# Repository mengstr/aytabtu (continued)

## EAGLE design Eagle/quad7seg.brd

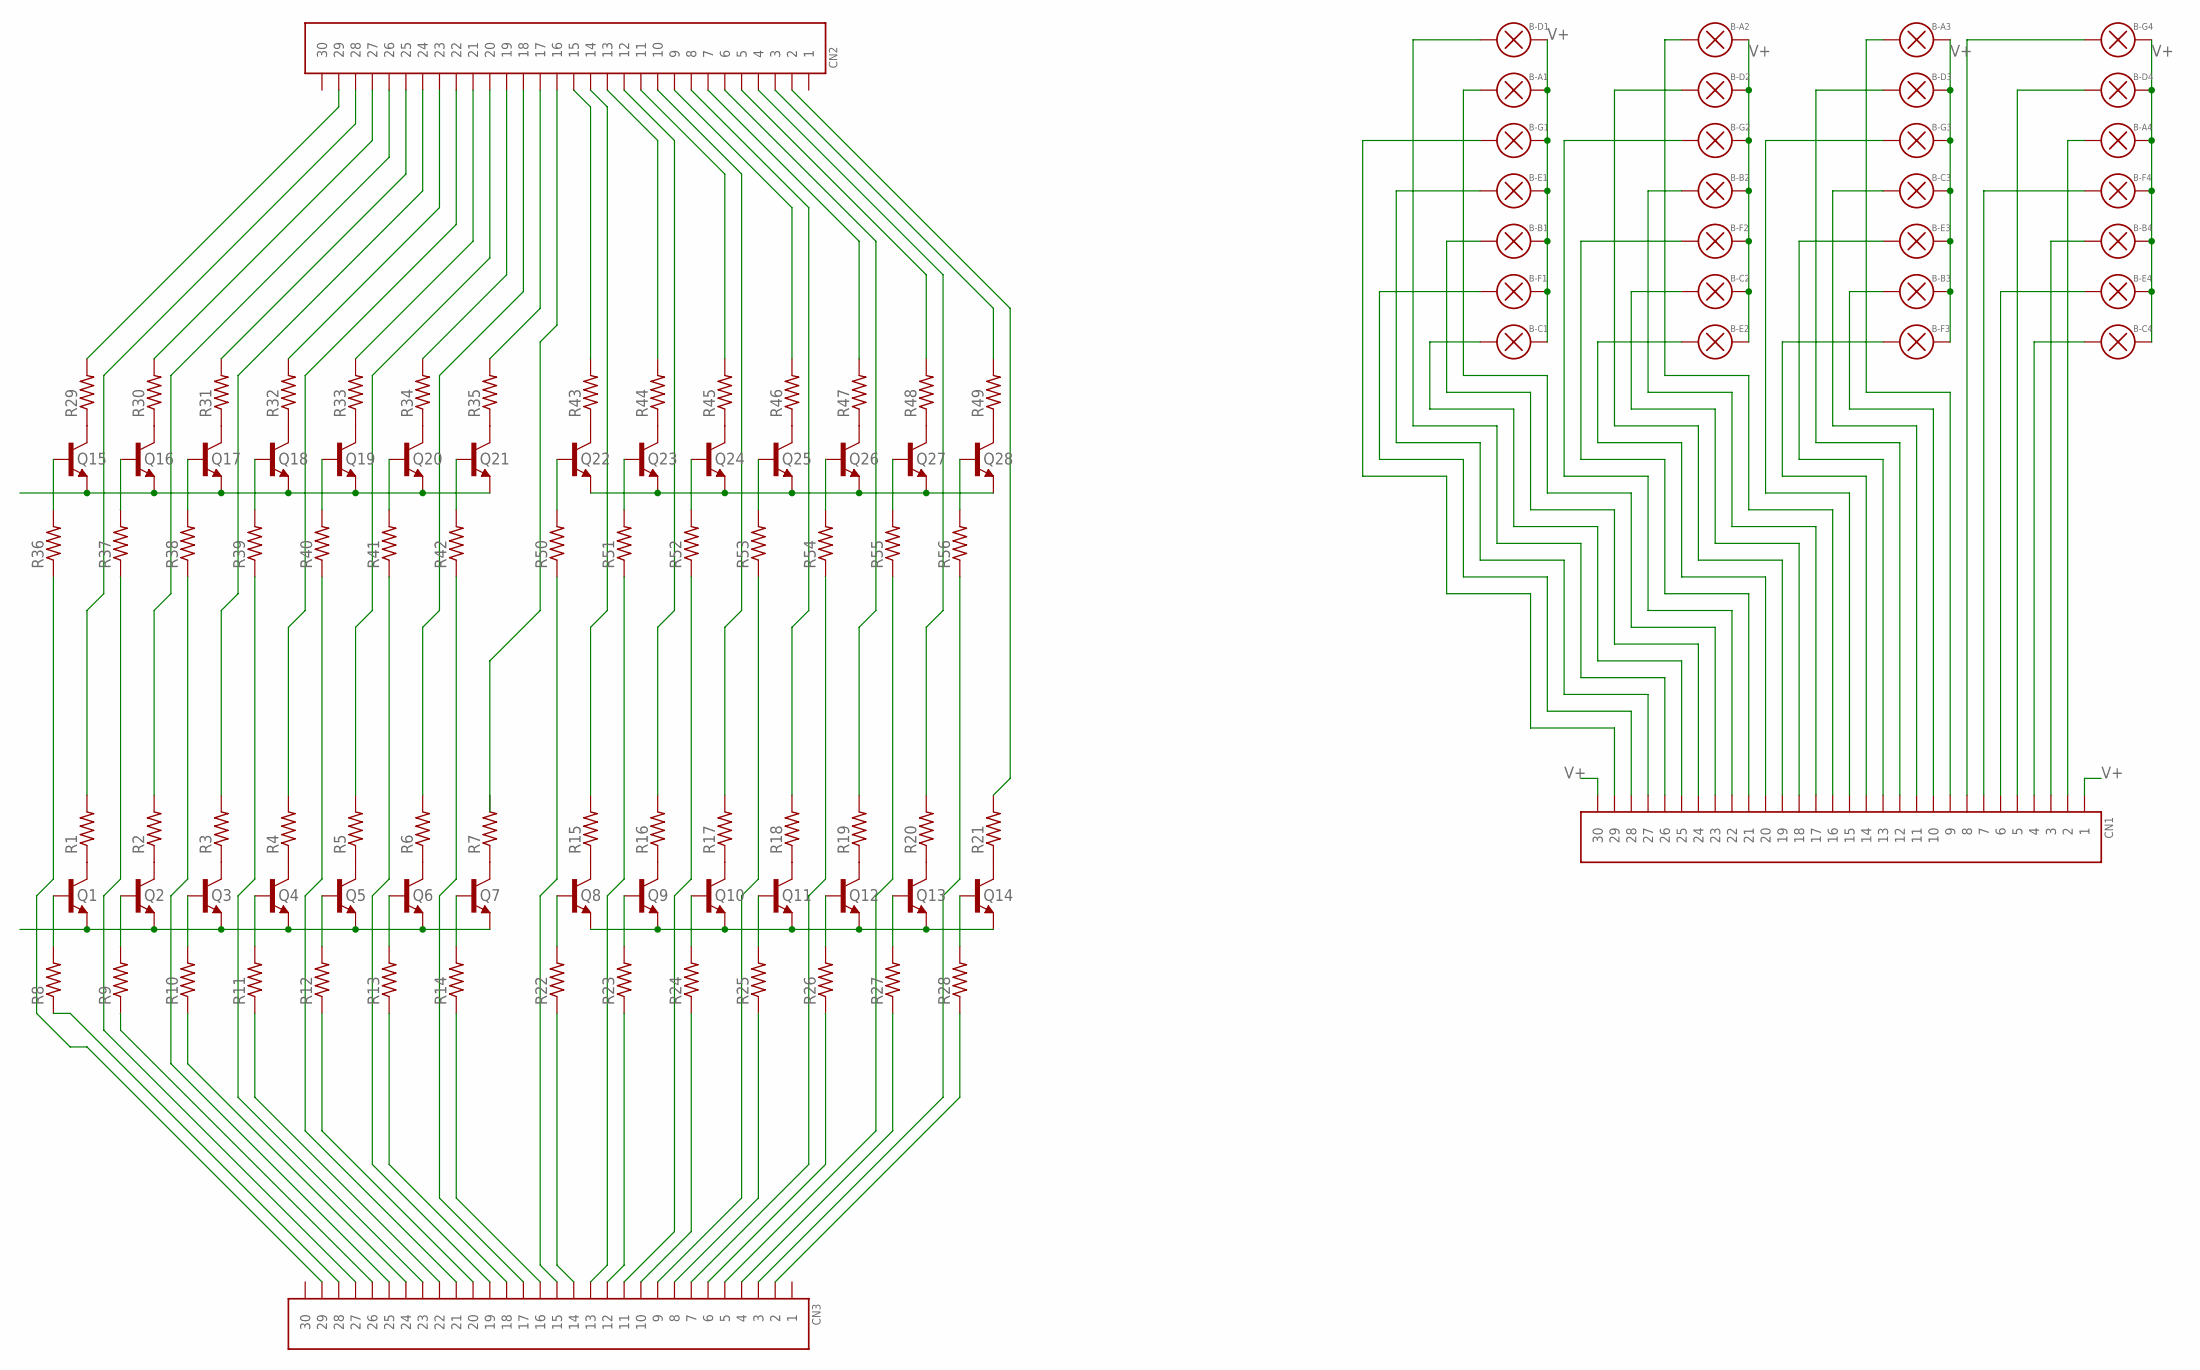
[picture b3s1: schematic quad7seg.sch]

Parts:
B-A1, B-A2, B-A3, B-A4: BULB-N; 4X11BULB1
B-B1, B-B2, B-B3, B-B4: BULB-F; 4X11BULB2
B-C1, B-C2, B-C3, B-C4: BULB-F; 4X11BULB2
B-D1, B-D2, B-D3, B-D4: BULB-N; 4X11BULB1
B-E1, B-E2, B-E3, B-E4: BULB-F; 4X11BULB2
B-F1, B-F2, B-F3, B-F4: BULB-F; 4X11BULB2
B-G1, B-G2, B-G3, B-G4: BULB-N; 4X11BULB1
CN1, CN2, CN3: HD30
Q1, Q2, Q3, Q4, Q5, Q6, Q7, Q8, Q9, Q10, Q11, Q12, Q13, Q14, Q15, Q16, Q17, Q18, Q19, Q20, Q21, Q22, Q23, Q24, Q25, Q26, Q27, Q28: 2N3904-1; TO92BH
R1, R2, R3, R4, R5, R6, R7, R8, R9, R10, R11, R12, R13, R14, R15, R16, R17, R18, R19, R20, R21, R22, R23, R24, R25, R26, R27, R28, R29, R30, R31, R32, R33, R34, R35, R36, R37, R38, R39, R40, R41, R42, R43, R44, R45, R46, R47, R48, R49, R50, R51, R52, R53, R54, R55, R56: R1/8-7.6MM; R0125-7.6

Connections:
GND: Q1.1 (E), Q2.1 (E), Q3.1 (E), Q4.1 (E), Q5.1 (E), Q6.1 (E), Q7.1 (E), Q8.1 (E), Q9.1 (E), Q10.1 (E), Q11.1 (E), Q12.1 (E), Q13.1 (E), Q14.1 (E), Q15.1 (E), Q16.1 (E), Q17.1 (E), Q18.1 (E), Q19.1 (E), Q20.1 (E), Q21.1 (E), Q22.1 (E), Q23.1 (E), Q24.1 (E), Q25.1 (E), Q26.1 (E), Q27.1 (E), Q28.1 (E)
unnamed: Q1.3 (C), R1.1
unnamed: Q2.3 (C), R2.1
unnamed: Q3.3 (C), R3.1
unnamed: Q4.3 (C), R4.1
unnamed: Q5.3 (C), R5.1
unnamed: Q6.3 (C), R6.1
unnamed: Q7.3 (C), R7.1
unnamed: Q1.2 (B), R8.2
unnamed: Q2.2 (B), R9.2
unnamed: Q3.2 (B), R10.2
unnamed: Q4.2 (B), R11.2
unnamed: Q5.2 (B), R12.2
unnamed: Q6.2 (B), R13.2
unnamed: Q7.2 (B), R14.2
unnamed: B-A4.P$1, CN1.P$2 (2)
unnamed: Q8.3 (C), R15.1
unnamed: Q9.3 (C), R16.1
unnamed: Q10.3 (C), R17.1
unnamed: Q11.3 (C), R18.1
unnamed: Q12.3 (C), R19.1
unnamed: Q13.3 (C), R20.1
unnamed: Q14.3 (C), R21.1
unnamed: Q8.2 (B), R22.2
unnamed: Q9.2 (B), R23.2
unnamed: Q10.2 (B), R24.2
unnamed: Q11.2 (B), R25.2
unnamed: Q12.2 (B), R26.2
unnamed: Q13.2 (B), R27.2
unnamed: Q14.2 (B), R28.2
unnamed: B-B4.P$1, CN1.P$3 (3)
unnamed: Q15.3 (C), R29.1
unnamed: Q16.3 (C), R30.1
unnamed: Q17.3 (C), R31.1
unnamed: Q18.3 (C), R32.1
unnamed: Q19.3 (C), R33.1
unnamed: Q20.3 (C), R34.1
unnamed: Q21.3 (C), R35.1
unnamed: Q15.2 (B), R36.2
unnamed: Q16.2 (B), R37.2
unnamed: Q17.2 (B), R38.2
unnamed: Q18.2 (B), R39.2
unnamed: Q19.2 (B), R40.2
unnamed: Q20.2 (B), R41.2
unnamed: Q21.2 (B), R42.2
unnamed: B-C4.P$1, CN1.P$4 (4)
unnamed: Q22.3 (C), R43.1
unnamed: Q23.3 (C), R44.1
unnamed: Q24.3 (C), R45.1
unnamed: Q25.3 (C), R46.1
unnamed: Q26.3 (C), R47.1
unnamed: Q27.3 (C), R48.1
unnamed: Q28.3 (C), R49.1
unnamed: Q22.2 (B), R50.2
unnamed: Q23.2 (B), R51.2
unnamed: Q24.2 (B), R52.2
unnamed: Q25.2 (B), R53.2
unnamed: Q26.2 (B), R54.2
unnamed: Q27.2 (B), R55.2
unnamed: Q28.2 (B), R56.2
unnamed: CN3.P$29 (29), R36.1
unnamed: CN2.P$3 (3), R49.2
unnamed: CN2.P$5 (5), R48.2
unnamed: CN2.P$7 (7), R47.2
unnamed: CN2.P$9 (9), R46.2
unnamed: CN2.P$11 (11), R45.2
unnamed: CN2.P$13 (13), R44.2
unnamed: CN2.P$15 (15), R43.2
unnamed: CN2.P$17 (17), R35.2
unnamed: CN2.P$19 (19), R34.2
unnamed: CN2.P$21 (21), R33.2
unnamed: CN2.P$23 (23), R32.2
unnamed: CN2.P$25 (25), R31.2
unnamed: CN2.P$27 (27), R30.2
unnamed: CN2.P$29 (29), R29.2
unnamed: CN2.P$2 (2), R21.2
unnamed: CN2.P$4 (4), R20.2
unnamed: CN2.P$6 (6), R19.2
unnamed: CN2.P$8 (8), R18.2
unnamed: CN2.P$10 (10), R17.2
unnamed: CN2.P$12 (12), R16.2
unnamed: CN2.P$14 (14), R15.2
unnamed: CN2.P$18 (18), R6.2
unnamed: CN2.P$20 (20), R5.2
unnamed: CN2.P$22 (22), R4.2
unnamed: CN2.P$24 (24), R3.2
unnamed: CN2.P$26 (26), R2.2
unnamed: CN2.P$28 (28), R1.2
unnamed: CN3.P$2 (2), R28.1
unnamed: CN3.P$4 (4), R27.1
unnamed: CN3.P$6 (6), R26.1
unnamed: CN3.P$8 (8), R25.1
unnamed: CN3.P$10 (10), R24.1
unnamed: CN3.P$12 (12), R23.1
unnamed: CN3.P$14 (14), R22.1
unnamed: CN3.P$16 (16), R14.1
unnamed: CN3.P$18 (18), R13.1
unnamed: CN3.P$20 (20), R12.1
unnamed: CN3.P$22 (22), R11.1
unnamed: CN3.P$24 (24), R10.1
unnamed: CN3.P$26 (26), R9.1
unnamed: CN3.P$28 (28), R8.1
unnamed: CN3.P$3 (3), R56.1
unnamed: CN3.P$5 (5), R55.1
unnamed: CN3.P$7 (7), R54.1
unnamed: CN3.P$9 (9), R53.1
unnamed: CN3.P$11 (11), R52.1
unnamed: CN3.P$13 (13), R51.1
unnamed: CN3.P$15 (15), R50.1
unnamed: CN3.P$17 (17), R42.1
unnamed: CN3.P$19 (19), R41.1
unnamed: CN3.P$21 (21), R40.1
unnamed: CN3.P$23 (23), R39.1
unnamed: CN3.P$25 (25), R38.1
unnamed: CN3.P$27 (27), R37.1
unnamed: B-D4.P$1, CN1.P$5 (5)
unnamed: B-E4.P$1, CN1.P$6 (6)
unnamed: B-F4.P$1, CN1.P$7 (7)
unnamed: B-G4.P$1, CN1.P$8 (8)
unnamed: B-A3.P$1, CN1.P$9 (9)
unnamed: B-B3.P$1, CN1.P$10 (10)
unnamed: B-C3.P$1, CN1.P$11 (11)
unnamed: B-D3.P$1, CN1.P$12 (12)
unnamed: B-E3.P$1, CN1.P$13 (13)
unnamed: B-F3.P$1, CN1.P$14 (14)
unnamed: B-G3.P$1, CN1.P$15 (15)
unnamed: B-A2.P$1, CN1.P$16 (16)
unnamed: B-B2.P$1, CN1.P$17 (17)
unnamed: B-C2.P$1, CN1.P$18 (18)
unnamed: B-D2.P$1, CN1.P$19 (19)
unnamed: B-E2.P$1, CN1.P$20 (20)
unnamed: B-F2.P$1, CN1.P$21 (21)
unnamed: B-G2.P$1, CN1.P$22 (22)
unnamed: B-A1.P$1, CN1.P$23 (23)
unnamed: B-B1.P$1, CN1.P$24 (24)
unnamed: B-C1.P$1, CN1.P$25 (25)
unnamed: B-D1.P$1, CN1.P$26 (26)
unnamed: B-E1.P$1, CN1.P$27 (27)
unnamed: B-F1.P$1, CN1.P$28 (28)
unnamed: B-G1.P$1, CN1.P$29 (29)
V+: B-A1.P$2, B-A2.P$2, B-A3.P$2, B-A4.P$2, B-B1.P$2, B-B2.P$2, B-B3.P$2, B-B4.P$2, B-C1.P$2, B-C2.P$2, B-C3.P$2, B-C4.P$2, B-D1.P$2, B-D2.P$2, B-D3.P$2, B-D4.P$2, B-E1.P$2, B-E2.P$2, B-E3.P$2, B-E4.P$2, B-F1.P$2, B-F2.P$2, B-F3.P$2, B-F4.P$2, B-G1.P$2, B-G2.P$2, B-G3.P$2, B-G4.P$2, CN1.P$1 (1), CN1.P$30 (30)

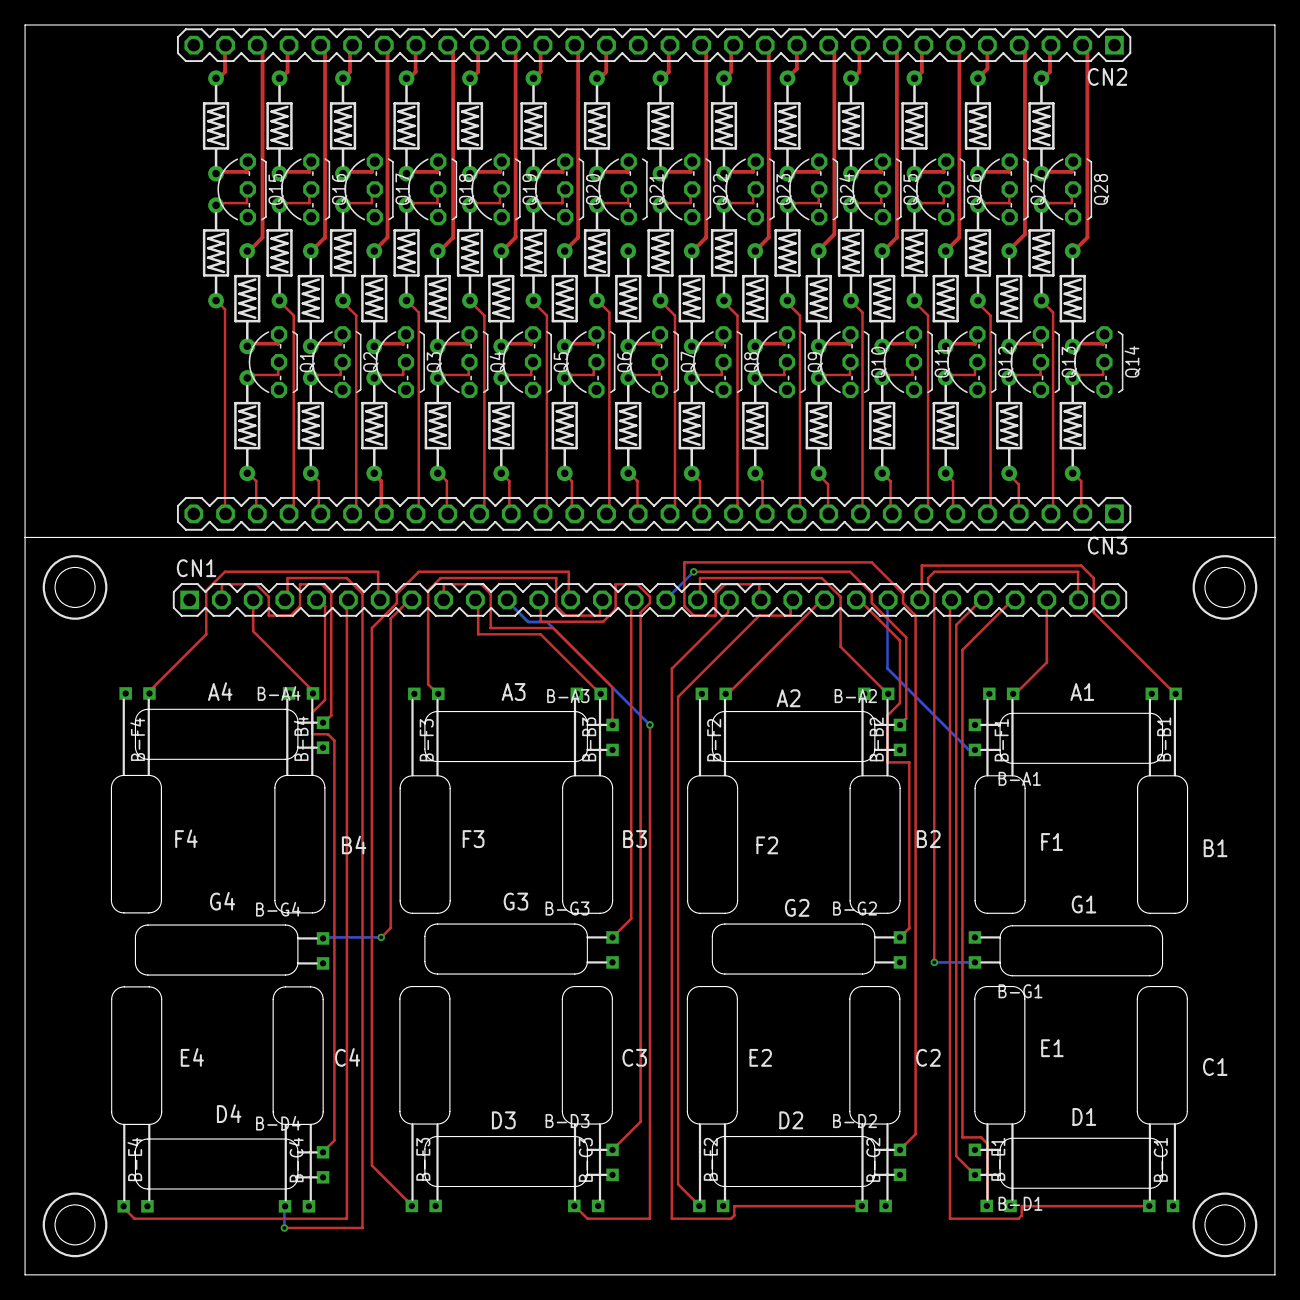
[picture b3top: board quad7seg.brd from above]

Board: 2 copper layers, 100.0 x 100.0 mm, 115 parts (0 on the bottom side), 141 nets.
